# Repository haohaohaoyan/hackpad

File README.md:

# mini mediapad

a small macropad for hack club's blueprint. it has a screen for a keys-per-second tracker (and maybe bad apple in the future), four keys for rhythm games, a rotary encoder for volume, and prev/pause/next track buttons. 

# Pictures

## Case (assembled, no parts because KiCad can't find them)

## Schematic

## PCB

## Bill of Materials:
- 1x Seeed Studio XIAO RP2040
- 1x 0.91in OLED display (128*32)
- 7x Cherry MX-style Keyswitches
- 7x Blank DSA Keycaps
- 1x EC11 Rotary Encoder
- 4x M3x16mm screws
- 4x M3x5mx4mm heatset inserts
- 3D printed case, top and bottom

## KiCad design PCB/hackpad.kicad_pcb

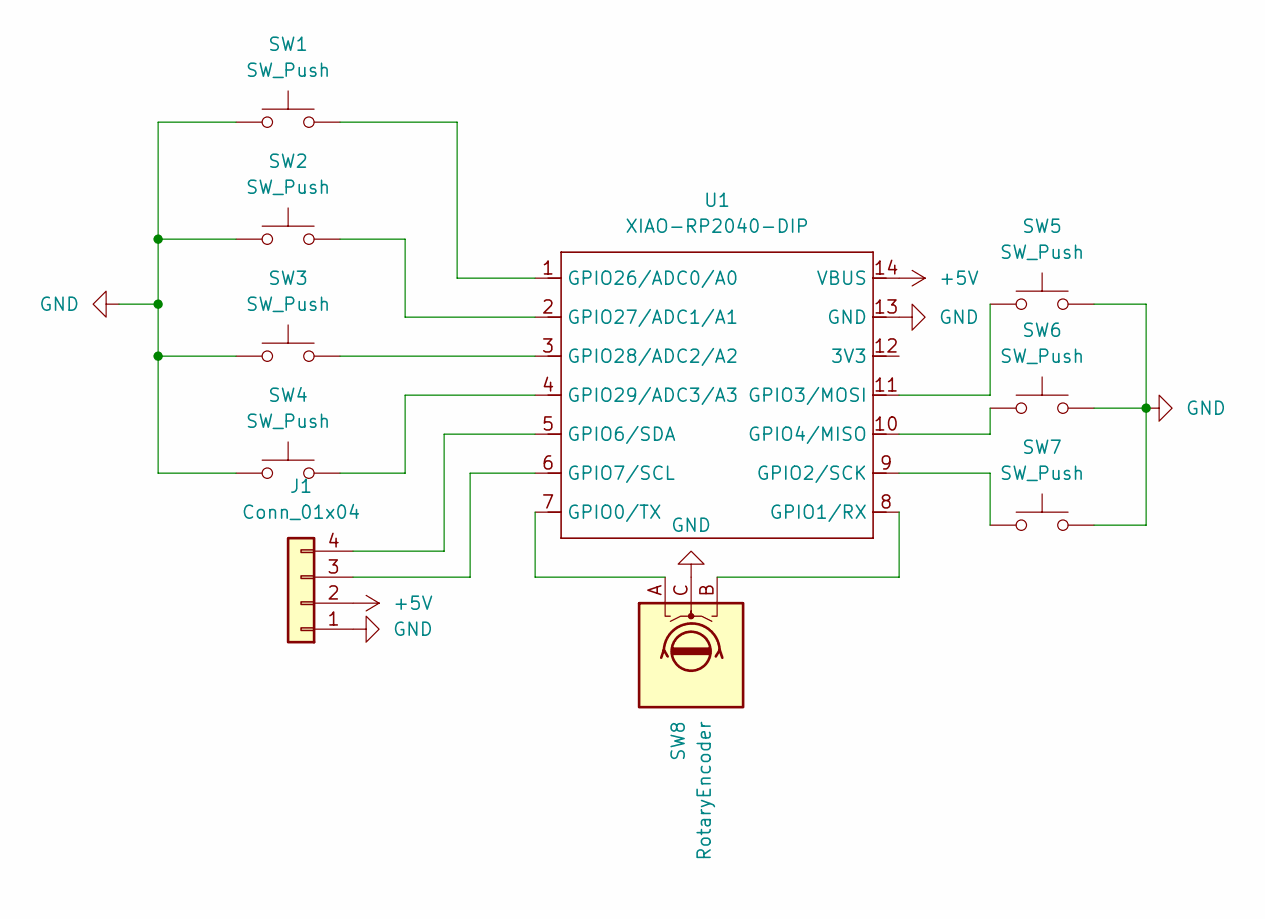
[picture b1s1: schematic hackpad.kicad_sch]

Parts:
J1: Conn_01x04; SSD1306-0.91-OLED-4pin-128x32
SW1, SW2, SW3, SW4, SW5, SW6, SW7: SW_Push; SW_Cherry_MX_1.00u_PCB
SW8: RotaryEncoder; RotaryEncoder_Alps_EC11E_Vertical_H20mm
U1: XIAO-RP2040-DIP

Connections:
+5V: J1.2 (VCC), U1.14 (VBUS)
GND: J1.1 (GND), SW1.1, SW2.1, SW3.1, SW4.1, SW5.2, SW6.2, SW7.2, SW8.C, U1.13 (GND)
unnamed: J1.3 (SCL), U1.6 (GPIO7/SCL)
unnamed: J1.4 (SDA), U1.5 (GPIO6/SDA)
unnamed: SW8.A, U1.7 (GPIO0/TX)
unnamed: SW8.B, U1.8 (GPIO1/RX)
unnamed: SW7.1, U1.9 (GPIO2/SCK)
unnamed: SW5.1, U1.11 (GPIO3/MOSI)
unnamed: SW6.1, U1.10 (GPIO4/MISO)
unnamed: SW1.2, U1.1 (GPIO26/ADC0/A0)
unnamed: SW2.2, U1.2 (GPIO27/ADC1/A1)
unnamed: SW3.2, U1.3 (GPIO28/ADC2/A2)
unnamed: SW4.2, U1.4 (GPIO29/ADC3/A3)

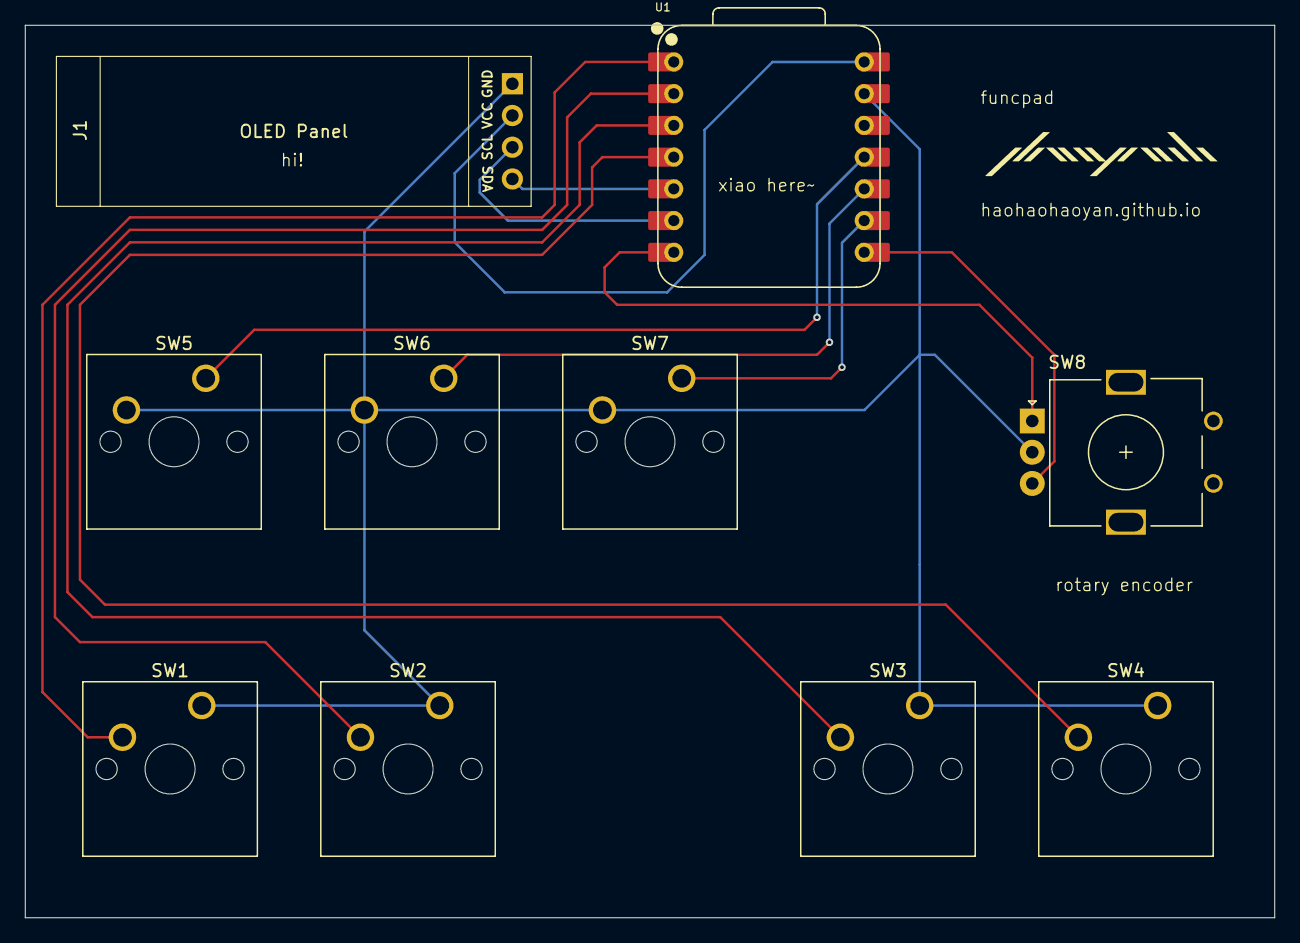
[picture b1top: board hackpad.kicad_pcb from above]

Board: 2 copper layers, 100.0 x 71.4 mm, 10 parts (0 on the bottom side), 13 nets.

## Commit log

2025-11-30 uploading everything atm
2025-12-06 update pcb, should be finished
2026-01-26 Upload case files
2026-01-26 Full hackpad in one file to meet submission requirements
2026-01-26 Move hackpad case to its own folder
2026-01-27 add new case
2026-01-27 move hackpad case
2026-01-28 pasted my firmware in from notepad
2026-01-28 upload readme pictures
2026-01-28 finished up readme for submission
2026-01-28 well i wrote the readme wrong so hopefully this fixes it
2026-01-28 well the last one didn't work so hopefully this one will
2026-01-28 oops i did the wrong file format and wasted 2 hours redoing it
2026-01-29 oh no apparently i just uploaded a blank pcb oops it should work now
